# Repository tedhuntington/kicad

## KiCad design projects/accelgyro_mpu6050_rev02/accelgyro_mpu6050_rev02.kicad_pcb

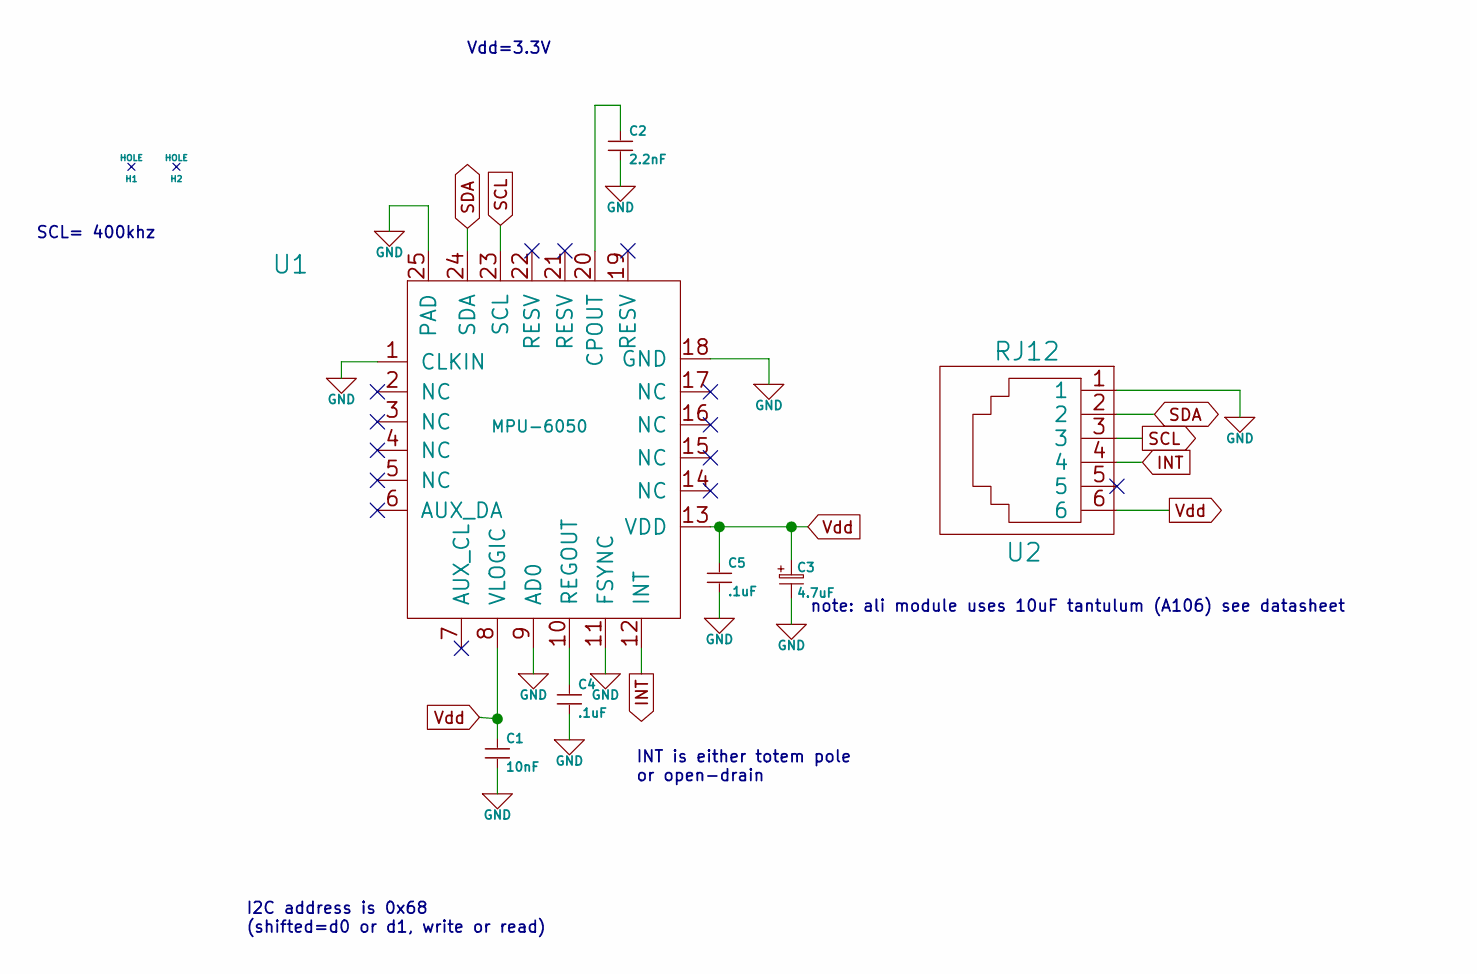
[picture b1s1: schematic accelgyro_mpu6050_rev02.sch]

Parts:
C1: 10nF; TED_SM0603_C
C2: 2.2nF; TED_SM0603_C
C3: 4.7uF; TED_SM2012_0805_ELEC_C
C4, C5: .1uF; TED_SM0603_C
H1, H2: HOLE; TED_Hole_2_6mm
U1: MPU-6050; TED_QFN24+1_NO_PASTE
U2: RJ12; TED_RJ12_Through_Hole

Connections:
GND: C1.2, C2.2, C3.2, C4.2, C5.2, U1.1 (CLKIN), U1.9 (AD0), U1.11 (FSYNC), U1.18 (GND), U1.25 (PAD), U2.1
INT: U1.12 (INT), U2.4
unnamed: C2.1, U1.20 (CPOUT)
unnamed: C4.1, U1.10 (REGOUT)
SCL: U1.23 (SCL), U2.3
SDA: U1.24 (SDA), U2.2
Vdd: C1.1, C3.1, C5.1, U1.8 (VLOGIC), U1.13 (VDD), U2.6

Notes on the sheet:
Vdd=3.3V
I2C address is 0x68 (shifted=d0 or d1, write or read)
INT is either totem pole or open-drain
SCL= 400khz
note: ali module uses 10uF tantulum (A106) see datasheet

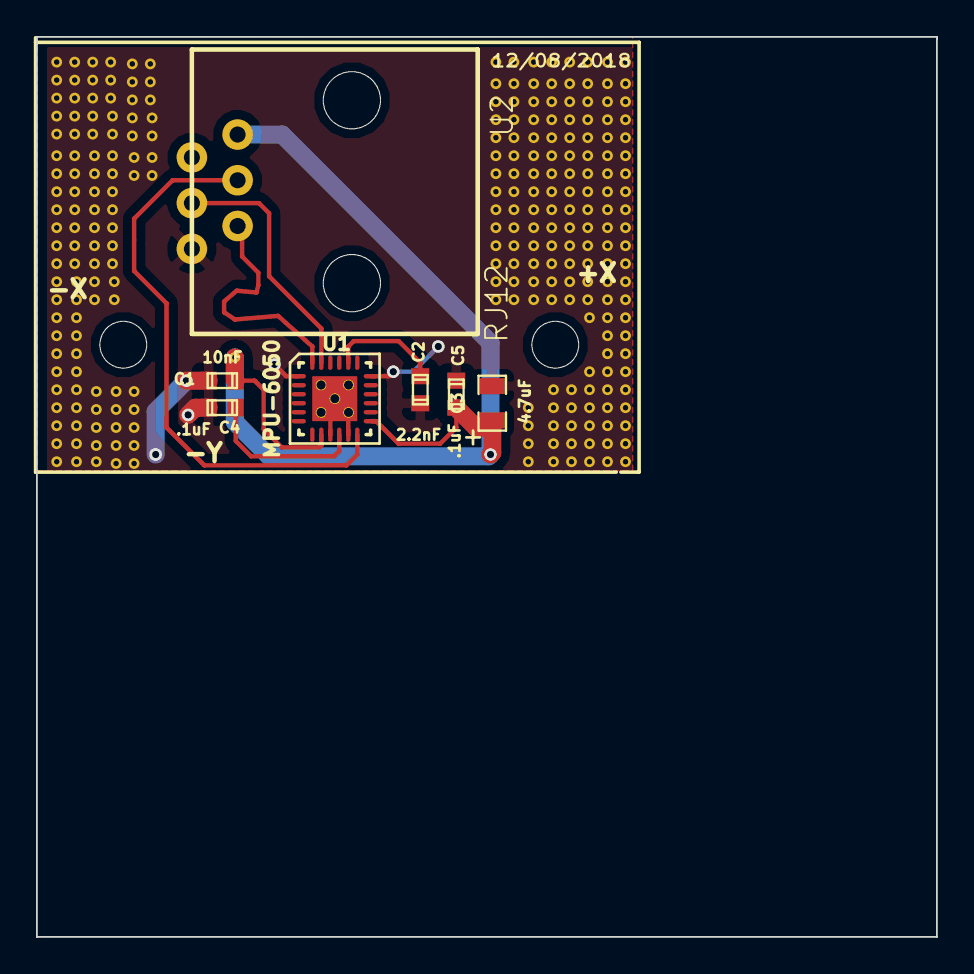
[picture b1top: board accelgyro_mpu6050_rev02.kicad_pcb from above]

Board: 2 copper layers, 50.0 x 50.0 mm, 9 parts (0 on the bottom side), 7 nets.

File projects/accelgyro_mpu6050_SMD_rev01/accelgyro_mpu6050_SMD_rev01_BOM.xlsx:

accelgyro_mpu6050_SMD_rev01
Sun 23 Jul 2017 10:05:59 AM PDT
Eeschema 4.0.6-e0-6349~53~ubuntu16.04.1
Component Count:9
Ref | Qnty | Value | Part | Part# | Unit Cost | Total Cost | Major Distributor | Minor Distributor
C1, | 1 | 10nF | capacitors:SM0603_C | VJ0603Y103MXAAC | 0.1 | 0.1 | Mouser
C2, | 1 | 2.2nF | capacitors:SM0603_C | GRM188R71H222KA01D | 0.1 | 0.1 | Digi-Key/Mouser
C3, | 1 | 4.7uF | capacitors:SM3216_1206_ELEC_C | TAJA475K025RNJ | 0.1 | 0.1 | Mouser
C4, C5, | 2 | .1uF | capacitors:SM0603_C | Vj0603V104ZXAPW1BC | 0.1 | 0.2 | Mouser
H1, H2, | 2 | HOLE | holes:Hole_2_6mm |  | 0 | 0
U1, | 1 | MPU-6050 | ICs:QFN24+1_NO_PASTE |  | 0.97 | 0.97 |  | AliExpress
U2, | 1 | RJ12 | connectors:RJ12_855135002 | 855135002 | 0.98 | 0.98 | Mouser
 |  |  |  |  |  | 2.45

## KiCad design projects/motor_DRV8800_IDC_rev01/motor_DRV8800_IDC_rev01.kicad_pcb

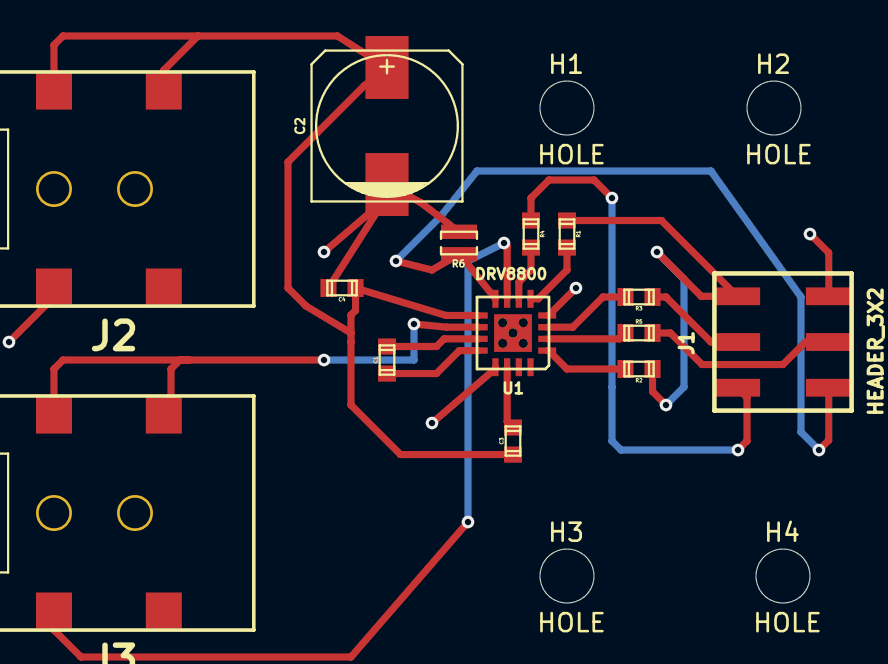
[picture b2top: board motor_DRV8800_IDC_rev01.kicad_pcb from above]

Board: 2 copper layers, 18 parts (0 on the bottom side), 17 nets.

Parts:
C1, C3, C4: .1uF (50v); TED_SM0603
C2: 100 uF (50v); TED_c_elec_8x10
H1, H2, H3, H4: HOLE; TED_Hole_3mm
J1: HEADER_3X2; TED_HEADER_3x2_SMT
J2, J3: DC_2.1MM; TED_DC_2.1mm_SMT
R1, R2: 3.3k; TED_SM0603
R3, R4, R5: 1k; TED_SM0603
R6: 10m; TED_SM0508-Reversed
U1: DRV8800; TED_QFN16+1

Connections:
CS: J1.4, R6.1, U1.8
GND: C2.2, C4.2, J1.6, J2.2, R6.2, U1.4, U1.13, U1.17
MODE: R5.1, U1.2
Motor1OutA: J3.2, U1.7
Motor1OutB: J3.1, U1.10
unnamed: C3.2, U1.14
unnamed: C1.2, U1.11
unnamed: C1.1, U1.12
unnamed: R2.2, U1.1
unnamed: R1.2, U1.5
unnamed: J1.3, R4.1
unnamed: J1.5, R5.2
unnamed: J1.2, R3.1
PHASE: R3.2, U1.3
PWM: R4.2, U1.6
VDD: J1.1, R1.1, R2.1
Vin: C2.1, C3.1, C4.1, J2.1, U1.9

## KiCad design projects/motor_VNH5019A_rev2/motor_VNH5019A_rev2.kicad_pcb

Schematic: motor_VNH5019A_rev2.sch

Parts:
C1, C2: .1uF (50v)
C3: 33nF
D1, D2, D3, D4: TVS_DIODE
J1, J3: TRM_3.5MM_2P; TED_TERMINAL_3.5MM_2PIN
J2: DC_2.1MM; TED_DC_2.1mm
J4: HEADER_9X2
R1, R2: 3.3k
R3, R4, R5: 1k
R6: 10k
R7: 1.5k
U1: VNH5019A-E

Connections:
+3.3v: J4.10, R1.2, R2.2
CS: R6.2, R7.2, U1.8 (CS)
GND: C1.2, C3.2, D2.2, D4.2, J1.2, J2.2, J4.9, R7.1, U1.6 (CS_DIS), U1.18 (GNDB), U1.19 (GNDB), U1.20 (GNDB), U1.26 (GNDA), U1.27 (GNDA), U1.28 (GNDA)
ICSPCLK_M1-: R5.1, U1.10 (INB)
ICSPDAT_M1+: R3.2, U1.4 (INA)
Motor1OutA: C2.1, D1.2, D2.1, J3.2, U1.1 (OUTA), U1.25 (OUTA), U1.30 (OUTA), U1.33 (OUTA/HEATSLG2)
Motor1OutB: C2.2, D3.2, D4.1, J3.1, U1.15 (OUTB), U1.16 (OUTB), U1.21 (OUTB), U1.32 (OUTB/HEATSLG3)
unnamed: J4.1, R3.1
unnamed: R2.1, U1.9 (ENB/DIAGB)
unnamed: R1.1, U1.5 (ENA/DIAGA)
unnamed: J4.18, R5.2
unnamed: J4.2, R4.1
unnamed: C3.1, J4.17, R6.1
PWM: R4.2, U1.7 (PWM)
Vin: C1.1, D1.1, D3.1, J1.1, J2.1, U1.3 (VCC), U1.12 (VBAT), U1.13 (VCC), U1.23 (VCC), U1.31 (VCC/HEATSLG1)

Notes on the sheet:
+5.5 to +24v
Out to Motor
Power source (Battery)
Alternative battery source (AC adapter)
PORT B (MALE, THROUGH-HOLE on bottom side)
clamp= 40V PESD15VS1UB,115
note:blocking capacitor replaced by TVS diodes
todo: compact to 6 pins (and probably IDC cable) (possibly 3 together)

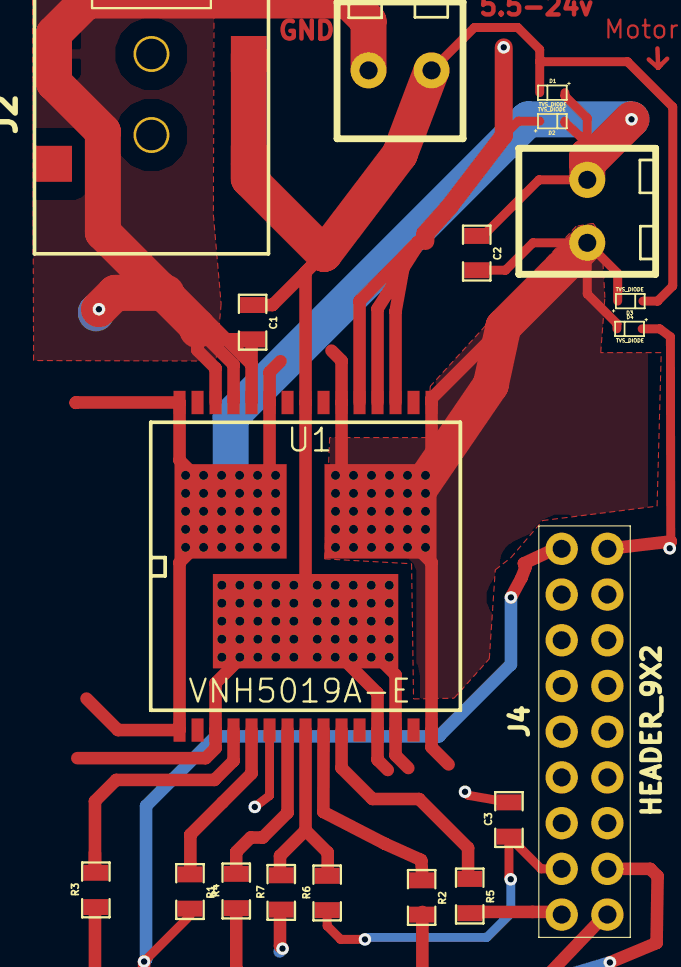
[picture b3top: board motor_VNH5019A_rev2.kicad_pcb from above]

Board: 2 copper layers, 19 parts (0 on the bottom side), 15 nets.

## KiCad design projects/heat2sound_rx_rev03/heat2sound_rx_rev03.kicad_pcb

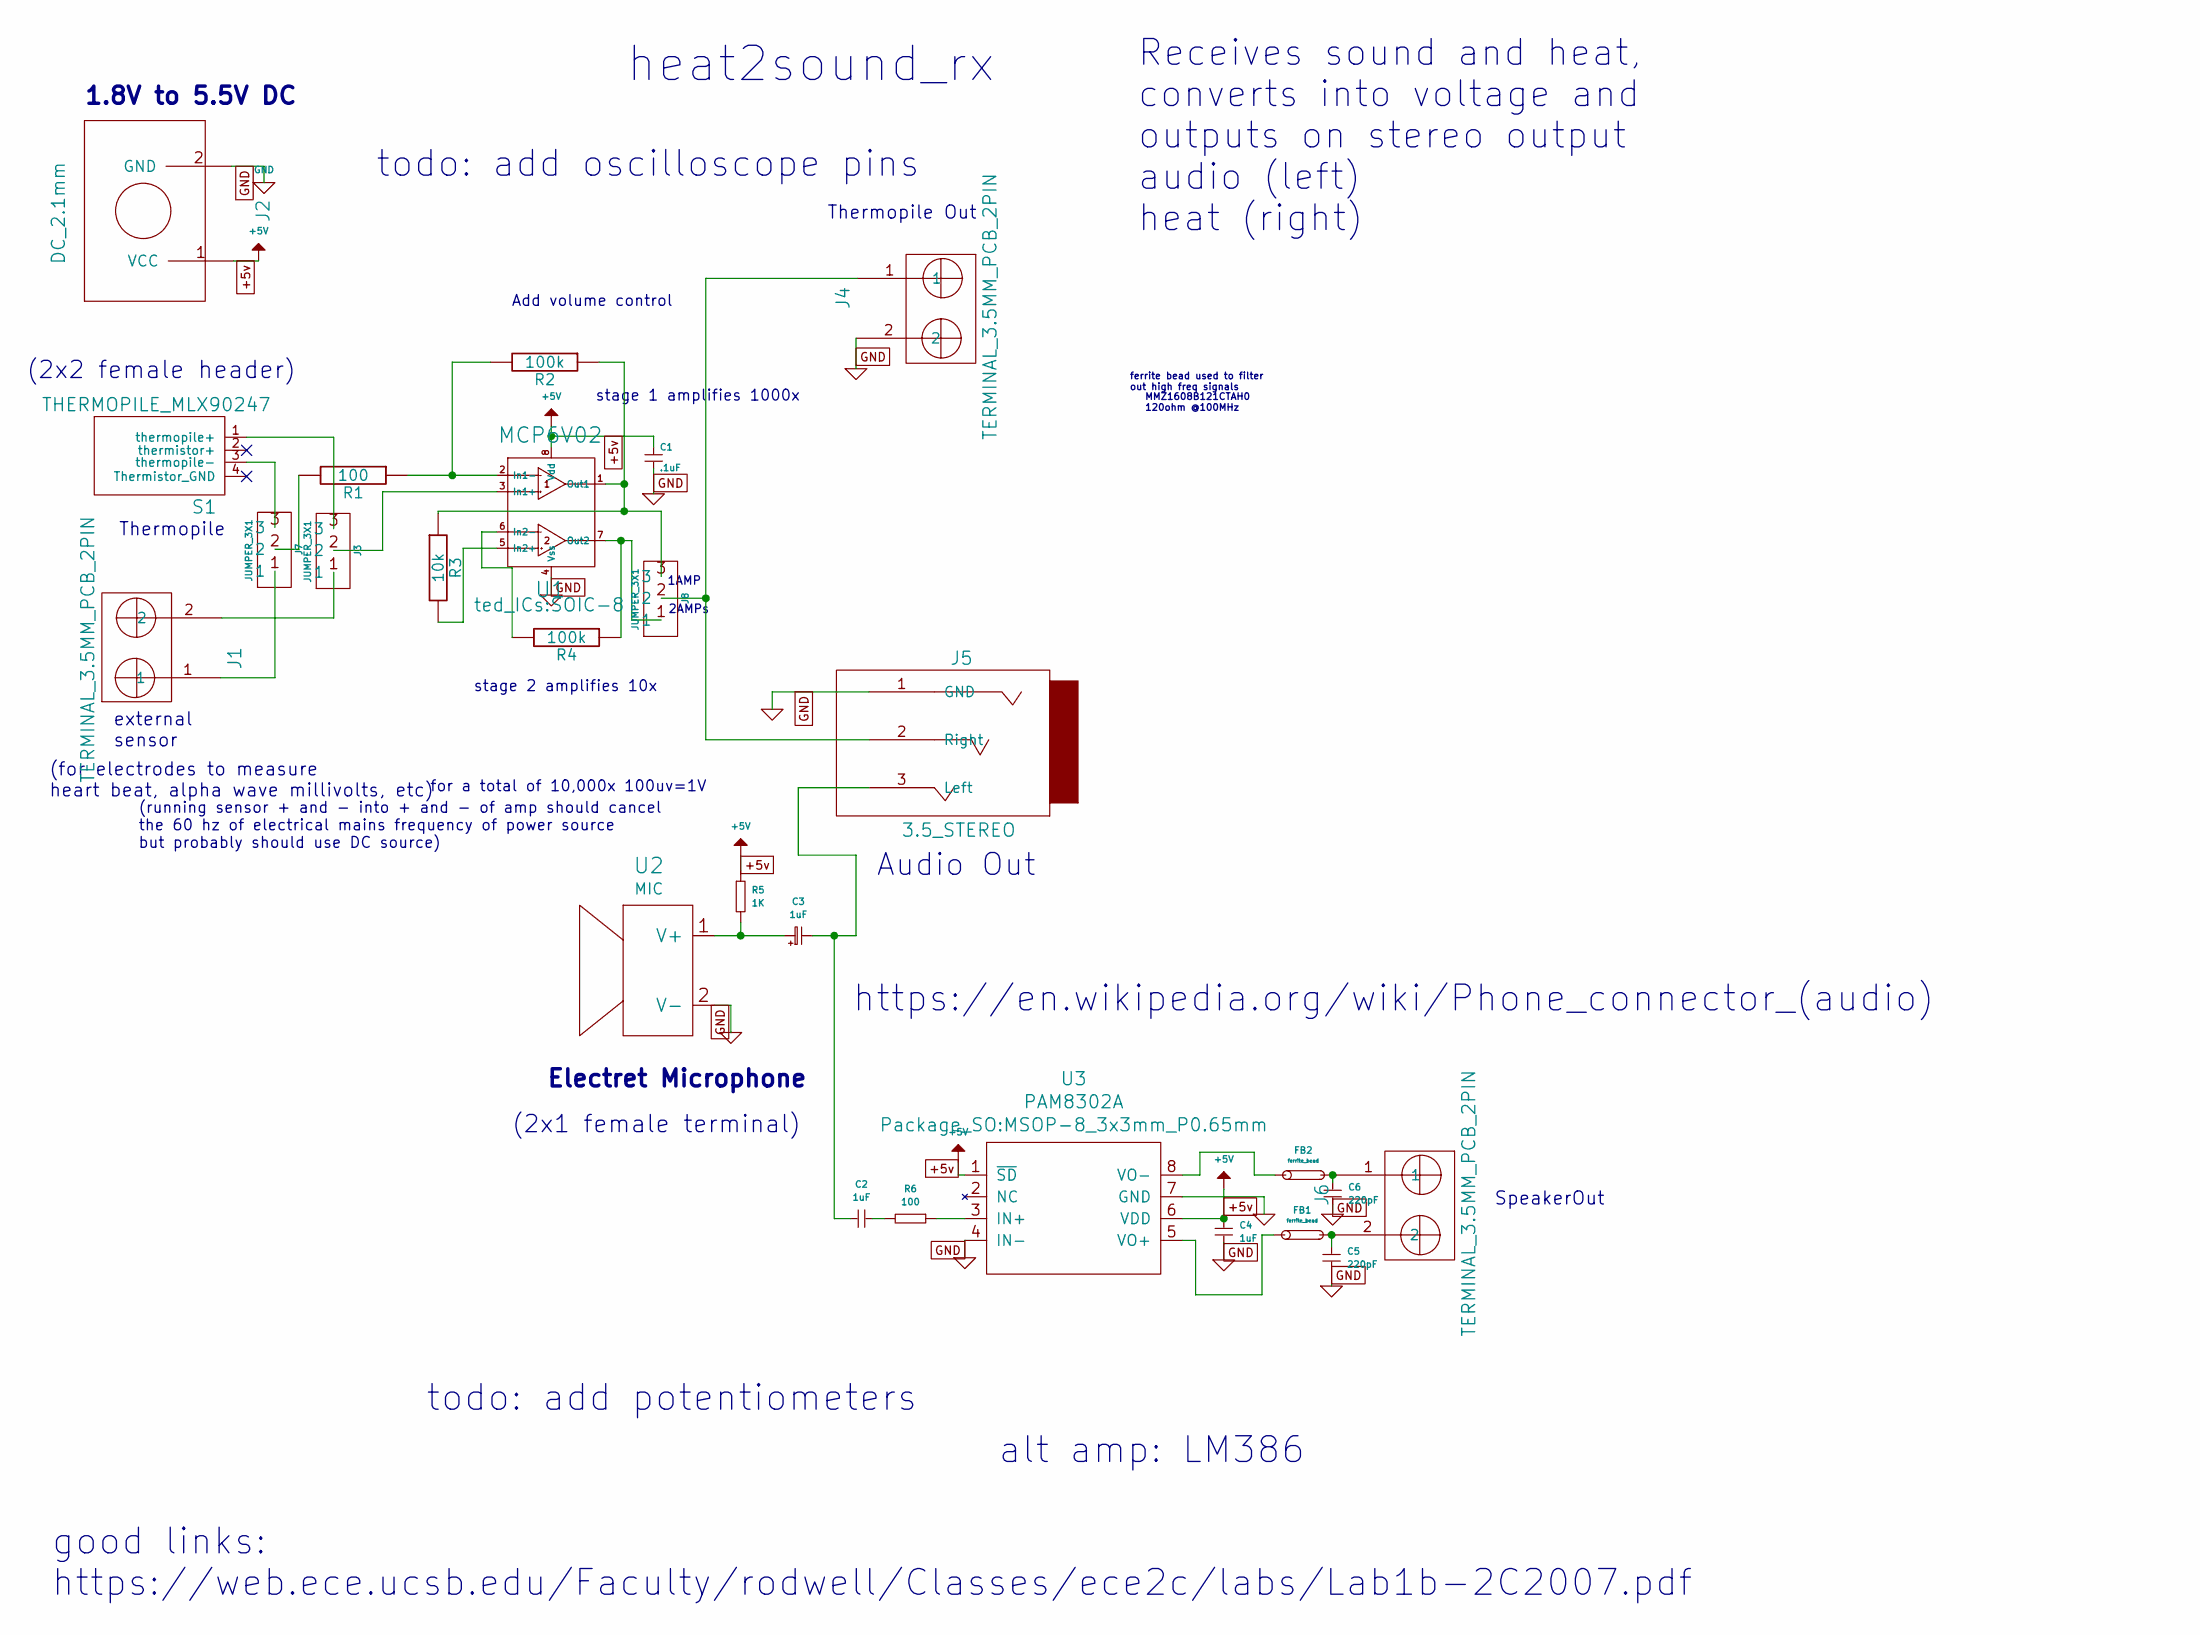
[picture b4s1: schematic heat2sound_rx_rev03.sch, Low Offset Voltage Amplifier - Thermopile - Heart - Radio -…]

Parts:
C1: .1uF; TED_SM0603_C
C2, C4: 1uF; TED_SM0603_C
C3: 1uF; TED_SM3528_1311_ELEC_C
C5, C6: 220pF; TED_SM0603_C
FB1, FB2: ferrite_bead; TED_SM0603_R
J1: TERMINAL_3.5MM_PCB_2PIN; TED_HEADER_2x1
J2: DC_2.1mm; TED_2.1mm_DC_SMD
J3, J7, J8: JUMPER_3X1; TED_HEADER_3x1
J4, J6: TERMINAL_3.5MM_PCB_2PIN; TED_TERMINAL_3.5MM_2PIN
J5: 3.5_STEREO; TED_3.5_Stereo_STX-3150-3N-1
R1, R6: 100; TED_SM0603_R
R2, R4: 100k; TED_SM0603_R
R3: 10k; TED_SM0603_R
R5: 1K; TED_SM0603_R
S1: THERMOPILE_MLX90247; TED_HEADER_2x2_THERMO
U1: MCP6V02; SOIC-8
U2: MIC; TED_HEADER_2x1
U3: PAM8302A; MSOP-8_3x3mm_P0.65mm

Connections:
+5v: C1.1, C4.1, J2.1 (VCC), R5.1, U1.8 (Vdd), U3.1 (~SD), U3.6 (VDD)
GND: C1.2, C4.2, C5.2, C6.2, J2.2 (GND), J4.2, J5.1 (GND), U1.4 (Vss), U2.2 (V-), U3.4 (IN-), U3.7 (GND)
unnamed: C2.1, R6.2
unnamed: C2.2, C3.2, J5.3 (Left)
unnamed: C3.1, R5.2, U2.1 (V+)
unnamed: C5.1, FB1.1, J6.2
unnamed: C6.1, FB2.1, J6.1
unnamed: FB1.2, U3.5 (VO+)
unnamed: FB2.2, U3.8 (VO-)
unnamed: J1.1, J7.1
unnamed: J1.2, J3.1
unnamed: J3.2, U1.3 (In1+)
unnamed: J3.3, S1.1 (thermopile+)
unnamed: J4.1, J5.2 (Right), J8.2
unnamed: J7.2, R1.2
unnamed: J7.3, S1.3 (thermopile-)
unnamed: J8.1, R4.1, U1.7 (Out2)
unnamed: J8.3, R2.1, R3.1, U1.1 (Out1)
unnamed: R1.1, R2.2, U1.2 (In1-)
unnamed: R3.2, U1.5 (In2+)
unnamed: R4.2, U1.6 (In2-)
unnamed: R6.1, U3.3 (IN+)

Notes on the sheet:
Add volume control
(running sensor + and - into + and - of amp should cancel the 60 hz of electrical mains frequency of power source but probably should use DC source)
stage 1 amplifies 1000x
for a total of 10,000x 100uv=1V
stage 2 amplifies 10x
Thermopile Out
Thermopile
external sensor
Audio Out
(for electrodes to measure heart beat, alpha wave millivolts, etc)
1.8V to 5.5V DC
heat2sound_rx
SpeakerOut
Electret Microphone
(2x1 female terminal)
(2x2 female header)
Receives sound and heat, converts into voltage and outputs on stereo output audio (left) heat (right)
ferrite bead used to filter out high freq signals
MMZ1608B121CTAH0 120ohm @100MHz
2AMPs
1AMP
todo: add oscilloscope pins
https://en.wikipedia.org/wiki/Phone_connector_(audio)
alt amp: LM386
todo: add potentiometers
good links: https://web.ece.ucsb.edu/Faculty/rodwell/Classes/ece2c/labs/Lab1b-2C2007.pdf

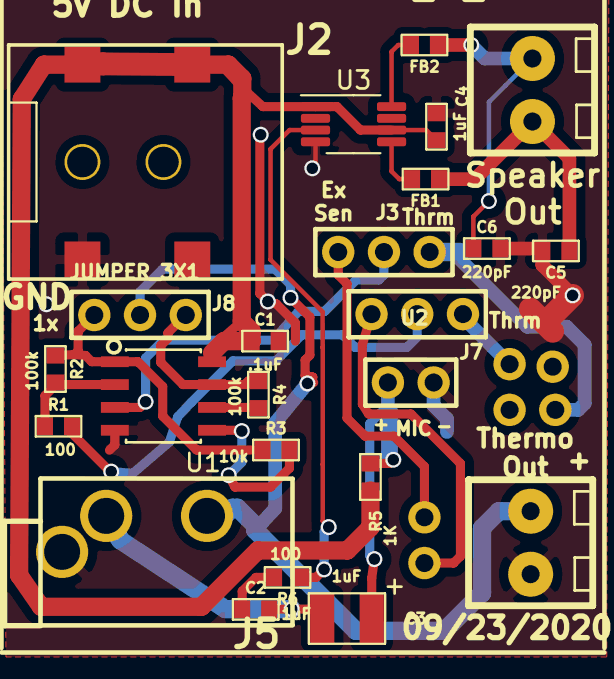
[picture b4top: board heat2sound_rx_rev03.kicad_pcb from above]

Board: 2 copper layers, 26 parts (0 on the bottom side), 22 nets.

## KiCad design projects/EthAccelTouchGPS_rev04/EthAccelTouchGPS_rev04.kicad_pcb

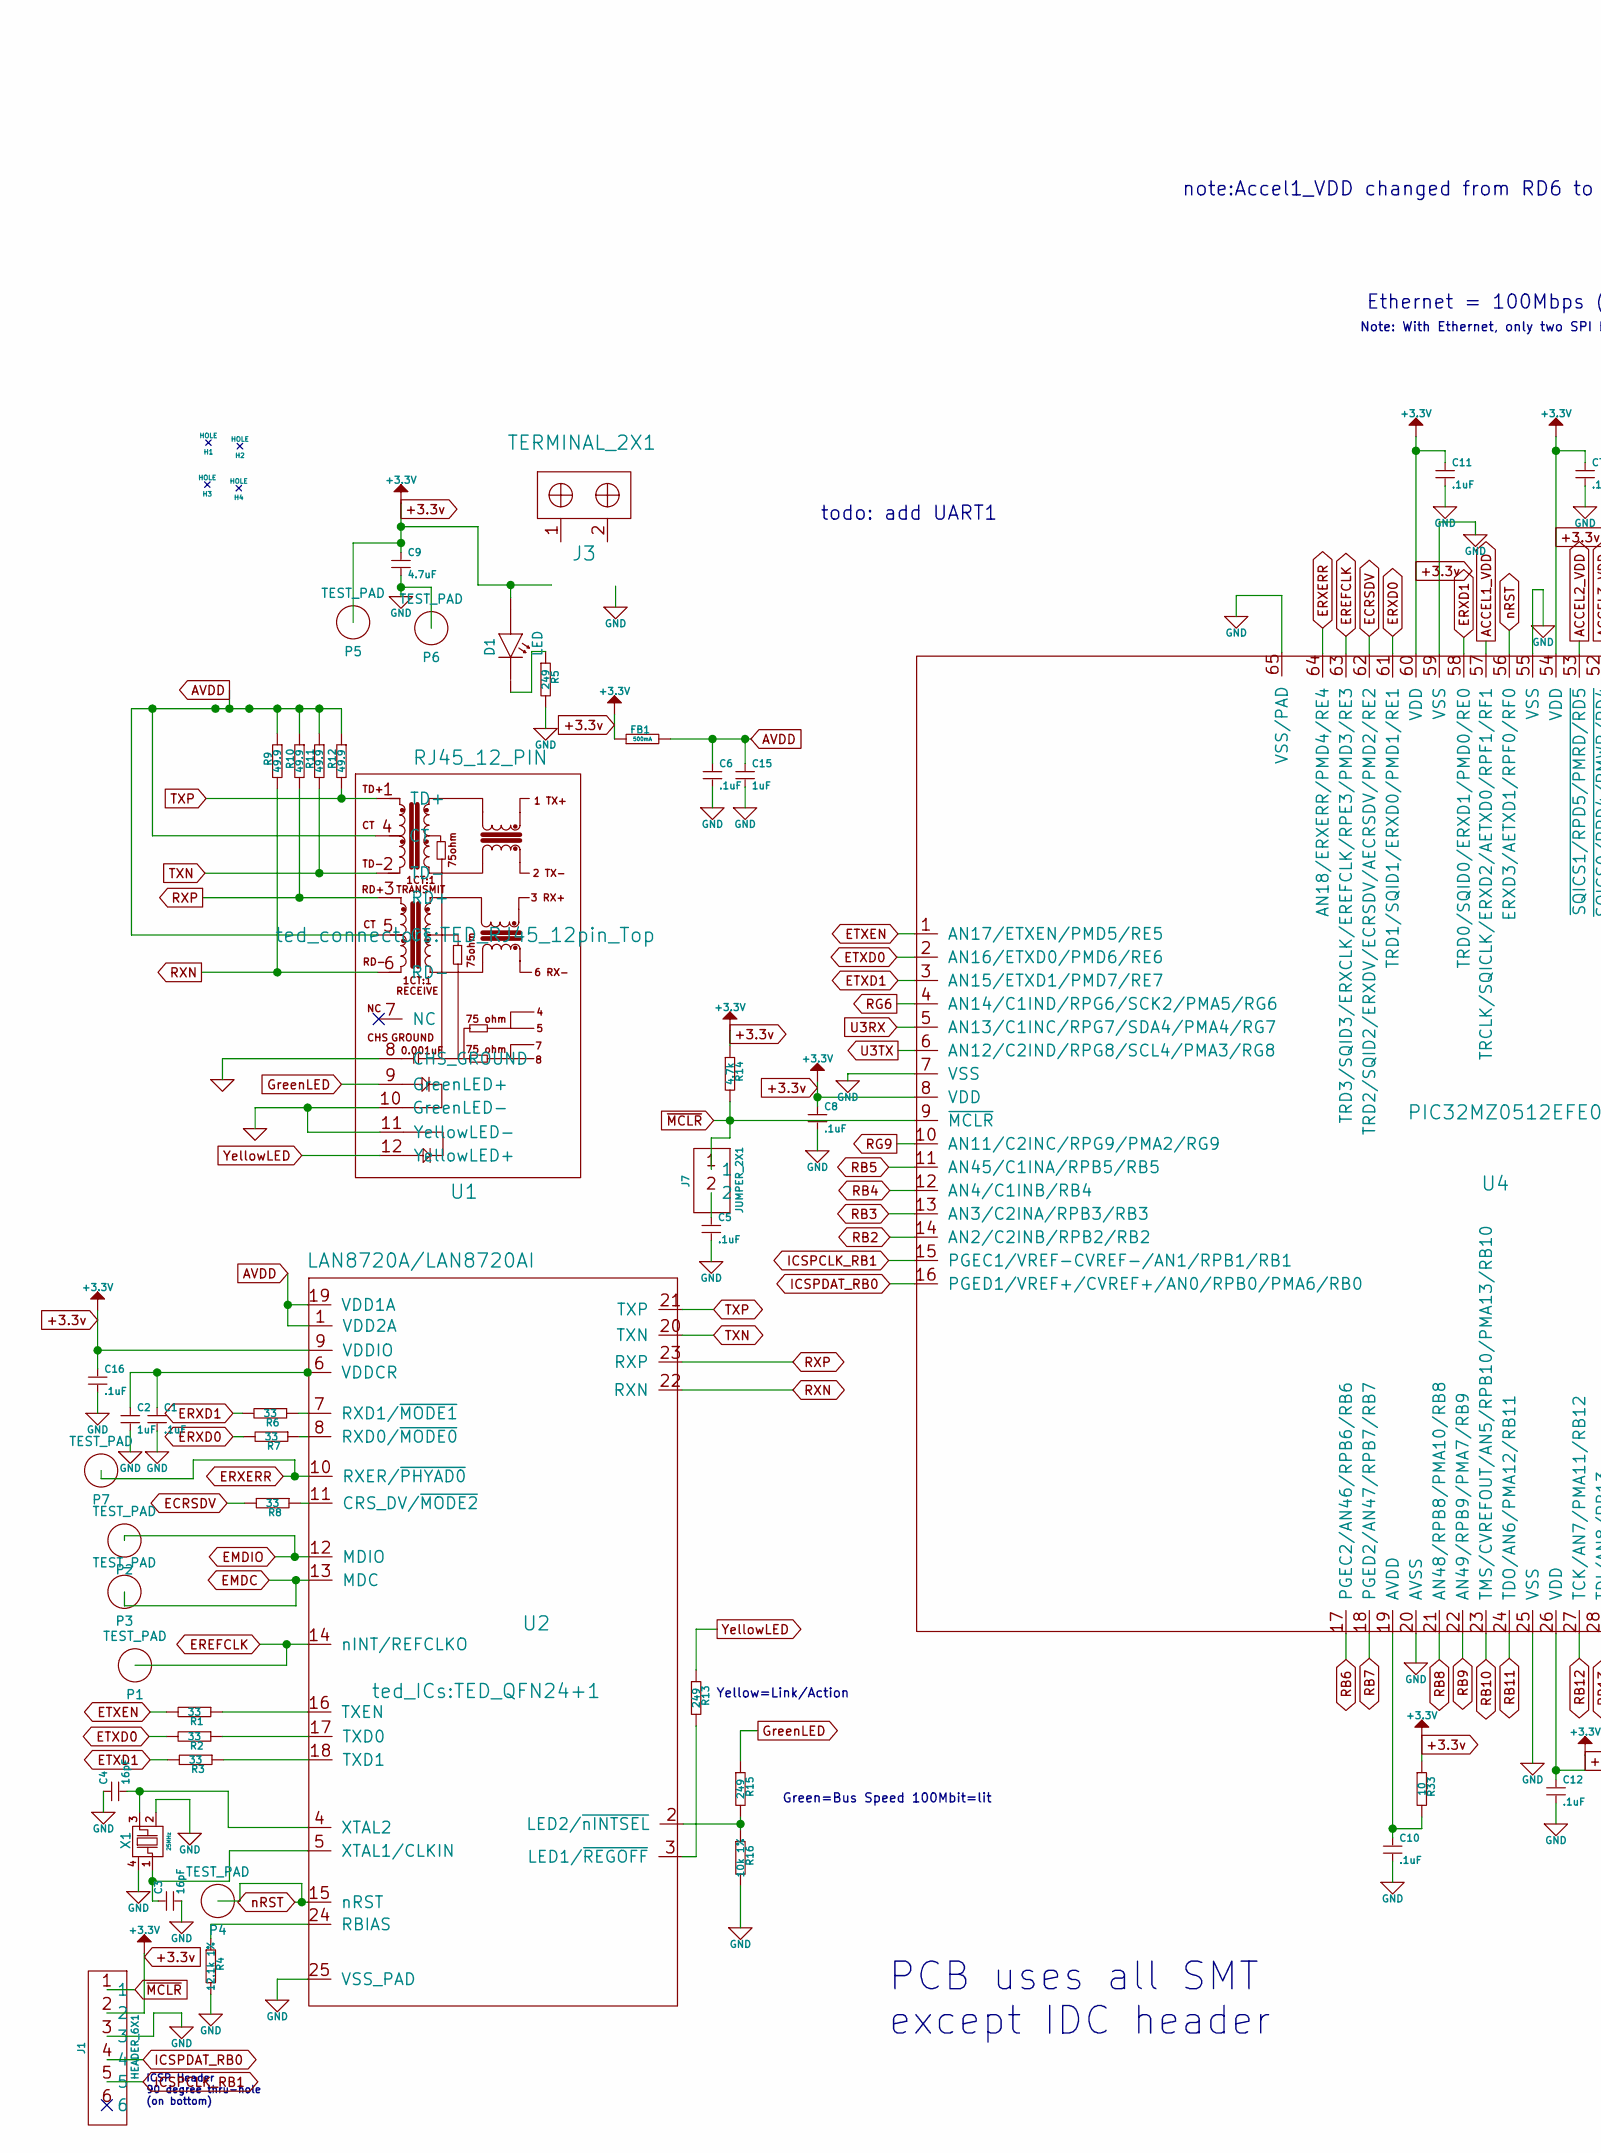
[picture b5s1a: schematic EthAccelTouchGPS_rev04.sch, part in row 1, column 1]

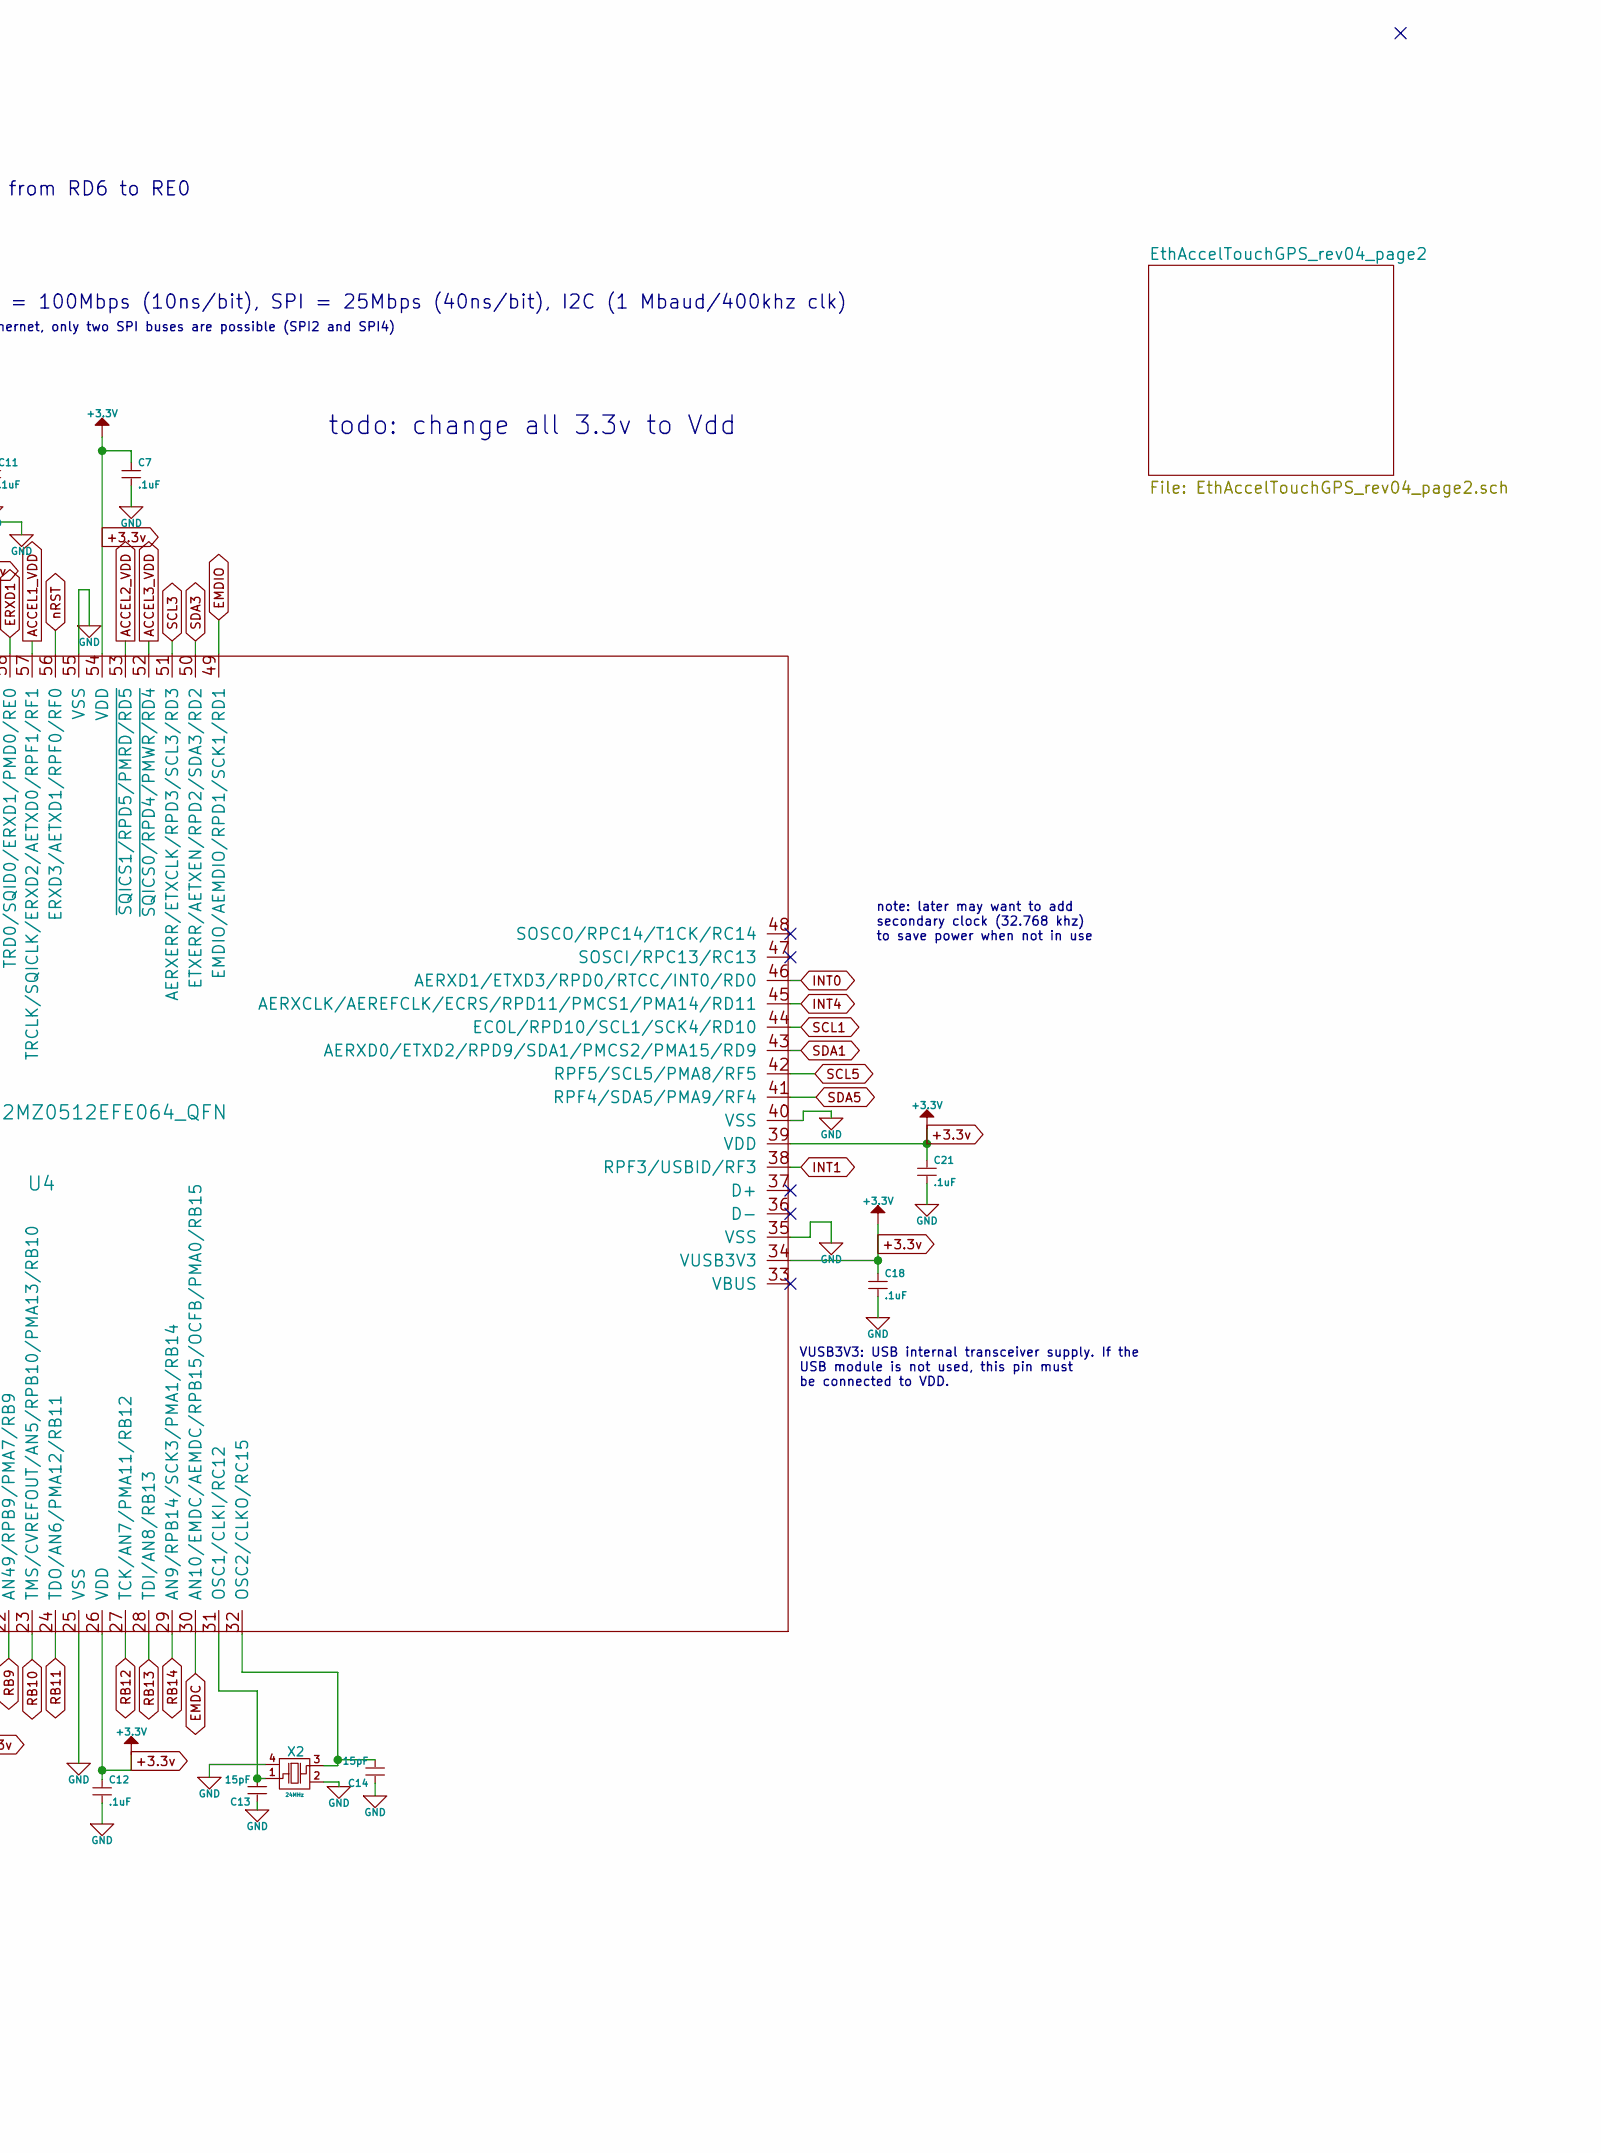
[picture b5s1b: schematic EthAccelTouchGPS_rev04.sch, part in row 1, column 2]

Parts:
C1, C5, C6, C7, C8, C10, C11, C12, C16, C18, C21: .1uF; TED_SM1608_0603_C
C2, C15: 1uF; TED_SM1608_0603_C
C3, C4: 16pF; TED_SM1608_0603_C
C9: 4.7uF; TED_SM1608_0603_C
C13, C14: 15pF; TED_SM1608_0603_C
D1: LED; TED_SM1206_LED
FB1: 500mA; TED_SM0805_R
H1, H2, H3, H4: HOLE; TED_Hole_3mm
J1: HEADER_6X1; TED_HEADER_6x1
J3: TERMINAL_2X1; TED_TERMINAL_SPRING_2.54MM_2PIN_1989748
J7: JUMPER_2X1; TED_JUMPER_2x1_SMD
P1, P2, P3, P4, P5, P6, P7: TEST_PAD; TED_TEST_PAD
R1, R2, R3, R6, R7, R8: 33; TED_SM0603_R
R4: 12.1k 1%; TED_SM0603_R
R5, R13, R15: 249; TED_SM0603_R
R9, R10, R11, R12: 49.9; TED_SM0603_R
R14: 4.7k; TED_SM0603_R
R16: 10k 1%; TED_SM0603_R
R33: 10; TED_SM0603_R
U1: RJ45_12_PIN; TED_RJ45_12pin_Top
U2: LAN8720A/LAN8720AI; TED_QFN24+1
U4: PIC32MZ0512EFE064_QFN; TED_QFN64+1H
X1: 25MHz; TED_crystal_FA-20H
X2: 24MHz; crystal_TSX3225

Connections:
+3.3v: C7.1, C8.1, C9.1, C11.1, C12.1, C16.1, C18.1, C21.1, D1.1 (A), FB1.1, J1.2, J3.1, P5.1, R14.1, R33.1, U2.9 (VDDIO), U4.8 (VDD), U4.26 (VDD), U4.34 (VUSB3V3), U4.39 (VDD), U4.54 (VDD), U4.60 (VDD); also elsewhere on the board
ACCEL1_VDD: U4.57 (TRCLK/SQICLK/ERXD2/AETXD0/RPF1/RF1); also elsewhere on the board
ACCEL2_VDD: U4.53 (~SQICS1/RPD5/PMRD/RD5); also elsewhere on the board
ACCEL3_VDD: U4.52 (~SQICS0/RPD4/PMWR/RD4); also elsewhere on the board
AVDD: C6.1, C15.1, FB1.2, R9.1, R10.1, R11.1, R12.1, U1.4 (CT), U1.5 (CT), U2.1 (VDD2A), U2.19 (VDD1A)
ECRSDV: R8.2, U4.62 (TRD2/SQID2/ERXDV/ECRSDV/AECRSDV/PMD2/RE2)
EMDC: P3.1, U2.13 (MDC), U4.30 (AN10/EMDC/AEMDC/RPB15/OCFB/PMA0/RB15)
EMDIO: P2.1, U2.12 (MDIO), U4.49 (EMDIO/AEMDIO/RPD1/SCK1/RD1)
EREFCLK: P1.1, U2.14 (nINT/REFCLKO), U4.63 (TRD3/SQID3/ERXCLK/EREFCLK/RPE3/PMD3/RE3)
ERXD0: R7.2, U4.61 (TRD1/SQID1/ERXD0/PMD1/RE1)
ERXD1: R6.2, U4.58 (TRD0/SQID0/ERXD1/PMD0/RE0)
ERXERR: P7.1, U2.10 (RXER/~PHYAD0~), U4.64 (AN18/ERXERR/PMD4/RE4)
ETXD0: R2.2, U4.2 (AN16/ETXD0/PMD6/RE6)
ETXD1: R3.2, U4.3 (AN15/ETXD1/PMD7/RE7)
ETXEN: R1.2, U4.1 (AN17/ETXEN/PMD5/RE5)
GND: C1.2, C2.2, C3.2, C4.1, C5.2, C6.2, C7.2, C8.2, C9.2, C10.2, C11.2, C12.2, C13.1, C14.1, C15.2, C16.2, C18.2, C21.2, J1.3, J3.2, P6.1, R4.2, R5.2, R16.2, U1.8 (CHS_GROUND), U1.10 (GreenLED-), U1.11 (YellowLED-), U2.25 (VSS_PAD), U4.7 (VSS), U4.20 (AVSS), U4.25 (VSS), U4.35 (VSS), U4.40 (VSS), U4.55 (VSS), U4.59 (VSS), U4.65 (VSS/PAD), X1.2, X1.4, X2.2, X2.4; also elsewhere on the board
GreenLED: R15.1, U1.9 (GreenLED+)
ICSPCLK_RB1: J1.5, U4.15 (PGEC1/VREF-CVREF-/AN1/RPB1/RB1); also elsewhere on the board
ICSPDAT_RB0: J1.4, U4.16 (PGED1/VREF+/CVREF+/AN0/RPB0/PMA6/RB0); also elsewhere on the board
INT0: U4.46 (AERXD1/ETXD3/RPD0/RTCC/INT0/RD0); also elsewhere on the board
INT1: U4.38 (RPF3/USBID/RF3); also elsewhere on the board
INT4: U4.45 (AERXCLK/AEREFCLK/ECRS/RPD11/PMCS1/PMA14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); also elsewhere on the board
unnamed: C1.1, C2.1, U2.6 (VDDCR)
unnamed: C3.1, U2.5 (XTAL1/CLKIN), X1.1
unnamed: C4.2, U2.4 (XTAL2), X1.3
unnamed: C5.1, J7.2
unnamed: C10.1, R33.2, U4.19 (AVDD)
unnamed: C13.2, U4.31 (OSC1/CLKI/RC12), X2.1
unnamed: C14.2, U4.32 (OSC2/CLKO/RC15), X2.3
unnamed: D1.2 (K), R5.1
unnamed: R1.1, U2.16 (TXEN)
unnamed: R2.1, U2.17 (TXD0)
unnamed: R3.1, U2.18 (TXD1)
unnamed: R4.1, U2.24 (RBIAS)
unnamed: R6.1, U2.7 (RXD1/~MODE1~)
unnamed: R7.1, U2.8 (RXD0/~MODE0~)
unnamed: R8.1, U2.11 (CRS_DV/~MODE2~)
unnamed: R13.2, U2.3 (LED1/~REGOFF~)
unnamed: R15.2, R16.1, U2.2 (LED2/~nINTSEL~)
RB2: U4.14 (AN2/C2INB/RPB2/RB2); also elsewhere on the board
RB3: U4.13 (AN3/C2INA/RPB3/RB3); also elsewhere on the board
RB4: U4.12 (AN4/C1INB/RB4); also elsewhere on the board
RB5: U4.11 (AN45/C1INA/RPB5/RB5); also elsewhere on the board
RB6: U4.17 (PGEC2/AN46/RPB6/RB6); also elsewhere on the board
RB7: U4.18 (PGED2/AN47/RPB7/RB7); also elsewhere on the board
RB8: U4.21 (AN48/RPB8/PMA10/RB8); also elsewhere on the board
RB9: U4.22 (AN49/RPB9/PMA7/RB9); also elsewhere on the board
RB10: U4.23 (TMS/CVREFOUT/AN5/RPB10/PMA13/RB10); also elsewhere on the board
RB11: U4.24 (TDO/AN6/PMA12/RB11); also elsewhere on the board
RB12: U4.27 (TCK/AN7/PMA11/RB12); also elsewhere on the board
RB13: U4.28 (TDI/AN8/RB13); also elsewhere on the board
RB14: U4.29 (AN9/RPB14/SCK3/PMA1/RB14); also elsewhere on the board
RG6: U4.4 (AN14/C1IND/RPG6/SCK2/PMA5/RG6); also elsewhere on the board
RG9: U4.10 (AN11/C2INC/RPG9/PMA2/RG9); also elsewhere on the board
RXN: R9.2, U1.6 (RD-), U2.22 (RXN)
RXP: R10.2, U1.3 (RD+), U2.23 (RXP)
SCL1: U4.44 (ECOL/RPD10/SCL1/SCK4/RD10); also elsewhere on the board
SCL3: U4.51 (AERXERR/ETXCLK/RPD3/SCL3/RD3); also elsewhere on the board
SCL5: U4.42 (RPF5/SCL5/PMA8/RF5); also elsewhere on the board
SDA1: U4.43 (AERXD0/ETXD2/RPD9/SDA1/PMCS2/PMA15/RD9); also elsewhere on the board
SDA3: U4.50 (ETXERR/AETXEN/RPD2/SDA3/RD2); also elsewhere on the board
SDA5: U4.41 (RPF4/SDA5/PMA9/RF4); also elsewhere on the board
TXN: R11.2, U1.2 (TD-), U2.20 (TXN)
TXP: R12.2, U1.1 (TD+), U2.21 (TXP)
U3RX: U4.5 (AN13/C1INC/RPG7/SDA4/PMA4/RG7); also elsewhere on the board
U3TX: U4.6 (AN12/C2IND/RPG8/SCL4/PMA3/RG8); also elsewhere on the board
YellowLED: R13.1, U1.12 (YellowLED+)
nRST: P4.1, U2.15 (nRST), U4.56 (ERXD3/AETXD1/RPF0/RF0)
~MCLR~: J1.1, J7.1, R14.2, U4.9 (~MCLR)

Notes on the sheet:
Ethernet = 100Mbps (10ns/bit), SPI = 25Mbps (40ns/bit), I2C (1 Mbaud/400khz clk)
ICSP Header 90 degree thru-hole (on bottom)
PCB uses all SMT except IDC header
Note: With Ethernet, only two SPI buses are possible (SPI2 and SPI4)
note: later may want to add secondary clock (32.768 khz) to save power when not in use
VUSB3V3: USB internal transceiver supply. If the USB module is not used, this pin must be connected to VDD.
Yellow=Link/Action
Green=Bus Speed 100Mbit=lit
todo: change all 3.3v to Vdd
note:Accel1_VDD changed from RD6 to RE0
todo: add UART1
